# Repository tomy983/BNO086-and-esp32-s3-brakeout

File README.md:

# BNO086-and-esp32-s3-brakeout
BNO086 + esp32-s3 brakeout 

This board uses micro ROS to publish imu sensor message and magnetic field sensor message to ROS2

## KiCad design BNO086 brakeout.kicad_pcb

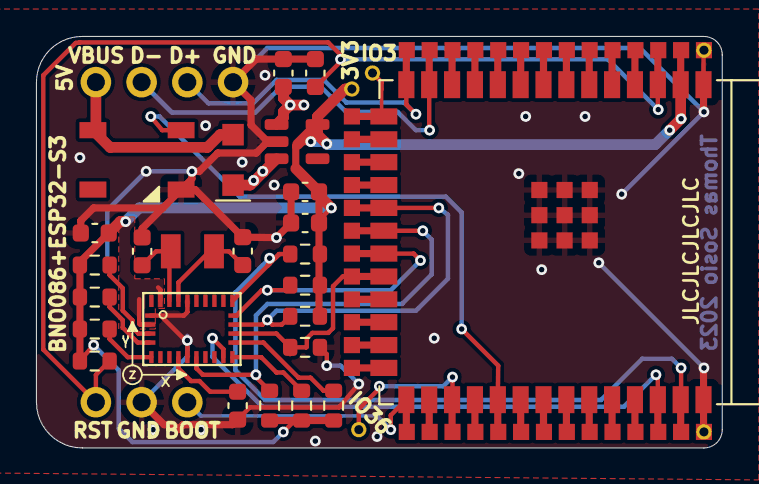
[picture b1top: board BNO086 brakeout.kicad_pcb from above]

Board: 2 copper layers, 38.1 x 22.9 mm, 27 parts (0 on the bottom side), 23 nets.

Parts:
C2, C8: 1uF; C_0603_1608Metric
C3: 10uF; C_0603_1608Metric
C4, C5, C9: 0.1uF; C_0603_1608Metric
C6, C7: 22pF; C_0603_1608Metric
D2: WS2812B; LED_WS2812B_PLCC4_5.0x5.0mm_P3.2mm
D3: 1N5819HW-7-F; Nexperia_CFP3_SOD-123W
J2: Conn_01x04_Pin; PinHeader_1x04_P2.54mm_Vertical
J3: Conn_01x03_Pin; PinSocket_1x03_P2.54mm_Vertical
R3, R5, R6, R7, R8, R9, R10, R11, R12, R13, R14: 10K; R_0603_1608Metric
U1: BNO086; BNO080
U2: ESP32-S3-WROOM-1
U4: XC6210B332MR; SOT-23-5
X1: 32.768; XTAL3215

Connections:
3.3V: C3.1, C5.1, C9.1, R3.1, R5.1, R6.1, R7.1, R8.1, R9.1, R10.1, R11.1, R12.1, R13.1, U1.3 (VDD), U1.28 (VDDIO), U2.2 (3V3), U4.5 (VOUT)
/5V: C2.1, D3.1 (K), U4.1 (VIN), U4.3 (CE)
/BOOT: R13.2, U1.4 (BOOTN)
/CAP: C4.2, U1.9 (CAP)
/CHIP_PU: C8.1, J3.3, R9.2, U2.3 (EN)
/CS: R11.2, U1.18 (H_CSN), U2.19 (GPIO11/TOUCH11/ADC2_CH0/FSPID/FSPIIO5/S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)
/D+: J2.3, U2.14 (GPIO20/U1CTS/ADC2_CH9/CLK_OUT1/USB_D+)
/D-: J2.2, U2.13 (GPIO19/U1RTS/ADC2_CH8/CLK_OUT2/USB_D-)
/INT: U1.14 (H_INTN), U2.38 (GPIO2/TOUCH2/ADC1_CH1)
/IO0: J3.1, U2.27 (GPIO0/BOOT)
/IO38: D2.4 (DIN), U2.31 (GPIO38/FSPIWP/SUBSPIWP)
/MOSI: R14.1, U1.17 (H_SA0/MOSI), U2.22 (GPIO14/TOUCH14/ADC2_CH3/FSPIWP/FSPIDQS/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)
/PS0/WAKE: R10.2, U1.6 (PS0/WAKE)
/PS1: R8.2, U1.5 (PS1)
/RST: R12.2, U1.11 (NRST), U2.20 (GPIO12/TOUCH12/ADC2_CH1/FSPICLK/FSPIIO6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)
/SCL/SCK/RX: R5.2, U1.19 (H_SCL/SCLK/RX), U2.21 (GPIO13/TOUCH13/ADC2_CH2/FSPIQ/FSPIIO7/S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)
/SDA/MISO/TX: R6.2, U1.20 (H_SDA/MISO/TX), U2.39 (GPIO1/TOUCH1/ADC1_CH0)
/S_SCL: R3.2, U1.15 (S_SCL)
/S_SDA: R7.2, U1.16 (S_SDA)
/VBUS: D2.1 (VDD), D3.2 (A), J2.1
/XIN: C6.1, U1.27 (XIN32), X1.P$1
/XOUT: C7.1, U1.26 (CLKSEL1/XOUT32), X1.P$2
GND: C2.2, C3.2, C4.1, C5.2, C6.2, C7.2, C8.2, C9.2, D2.3 (VSS), J2.4, J3.2, R14.2, U1.2 (GND), U1.10 (CLKSEL0), U1.25 (GNDIO), U2.1 (GND), U2.40 (GND), U2.41 (GND), U4.2 (GND)

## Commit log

2023-09-08 Create PCB
2023-09-08 Create pcb creation
2023-09-08 Rename BNO086 brakeout.kicad_prl to PCB/BNO086 brakeout.kicad_prl
2023-09-08 Rename BNO086 brakeout.kicad_pro to PCB/BNO086 brakeout.kicad_pro
2023-09-08 Rename TEST_FW/main.cpp to TEST_FW/src/main.cpp
